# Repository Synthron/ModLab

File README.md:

# ModLab

## A modular station for your electronic workbench

The ModLab is designed to be housed in a 19" Rack with 3U.  
It is the improved version of the (failed) Arduino Workstation I built a long time ago.

But now It will be bigger, better and way too complicated.

---

[GitHub](https://github.com/Synthron/ModLab)
[Gitlab](https://gitlab.synthron.de/Synthron/ModLab)

---

**Work in Progress**

---

# To-Dos

## Repo

- [X] Rewrite documentation in english
  - [ ] Write better introduction
  - [ ] explain what exactly the ModLab is
  - [X] update changes for TFT
  - [X] Explain TFT Protocol
  - [ ] Attach Schematics
- [X] Cleanup Repo

---

## Hardware

- [X] Redesign modules with STM32
  - [x] Master Bus Controller with F767
    - [X] V1
      - [X] Review
      - [X] Ordered
      - [X] Assembled
    - [ ] V2
      - [ ] Change LCD connector
      - [ ] omit external SRAM
      - [ ] include header for Reset
  - [x] Diode/LED-Tester
    - [X] V1
    - [X] V2
  - [X] Variable Power Supply
    - [X] V1
    - [ ] V2
      - [X] Fix Relais Footprint
      - [X] Feedback Dividers for correct level
      - [ ] Review
      - [ ] Ordered
      - [ ] Assembled
  - [x] Symmetric Power Supply
    - [X] V1
    - [ ] V2
      - [X] fix negative channel
      - [X] fix CC LEDs
      - [ ] Review
      - [ ] Ordered
      - [ ] Assembled
  - [x] Waveform generator
  - [ ] DSO-138 clone?
  - [X] Electronic Load
  - [ ] Logic Tester
  - [ ] Continuity tester
  - [ ] Speaker Module
  - [x] Termination boards and Bus Extenders

---

## Software

- General
  - [X] Define CAN Protocol
    - [X] Define Command Structure
    - [X] Define Data Structure
- Master Bus Controller
  - [ ] STM32 code
    - [X] USB for Debug
    - [X] LCD
      - [X] Get Nextion Display working
        - [X] UI
        - [X] µC Interface
    - [ ] Busses
      - [X] CAN
      - [ ] SPI - No Usecase so far
      - [ ] I2C
      - [ ] DAC - No Usecase so far
      - [ ] RS485 - No Usecase so far
  - [ ] ESP32 code
    - [ ] comm with STM
    - [X] OTA
    - [ ] basic web interface
- Diode Tester code
  - [X] CAN
  - [X] Testing Sequence
  - [X] ADC
- SymPSU
  - [X] PWM Signals
  - [X] ADC
  - [X] CAN-Interface
- Power SMPS
  - [X] PWM Signals
  - [X] ADC
  - [X] CAN-Interface
- Waveform Generator
  - [X] PWM Signals
  - [X] AD9833
  - [X] CAN-Interface
- Power Monitor
  - [ ] Voltage Measurement
  - [ ] Current Measurement
  - [ ] I2C communication

---

ModLab Lib Tracker:

1. SymPSU
2. Diode-Tester
3. SMPS
4. Load
5. F-Gen

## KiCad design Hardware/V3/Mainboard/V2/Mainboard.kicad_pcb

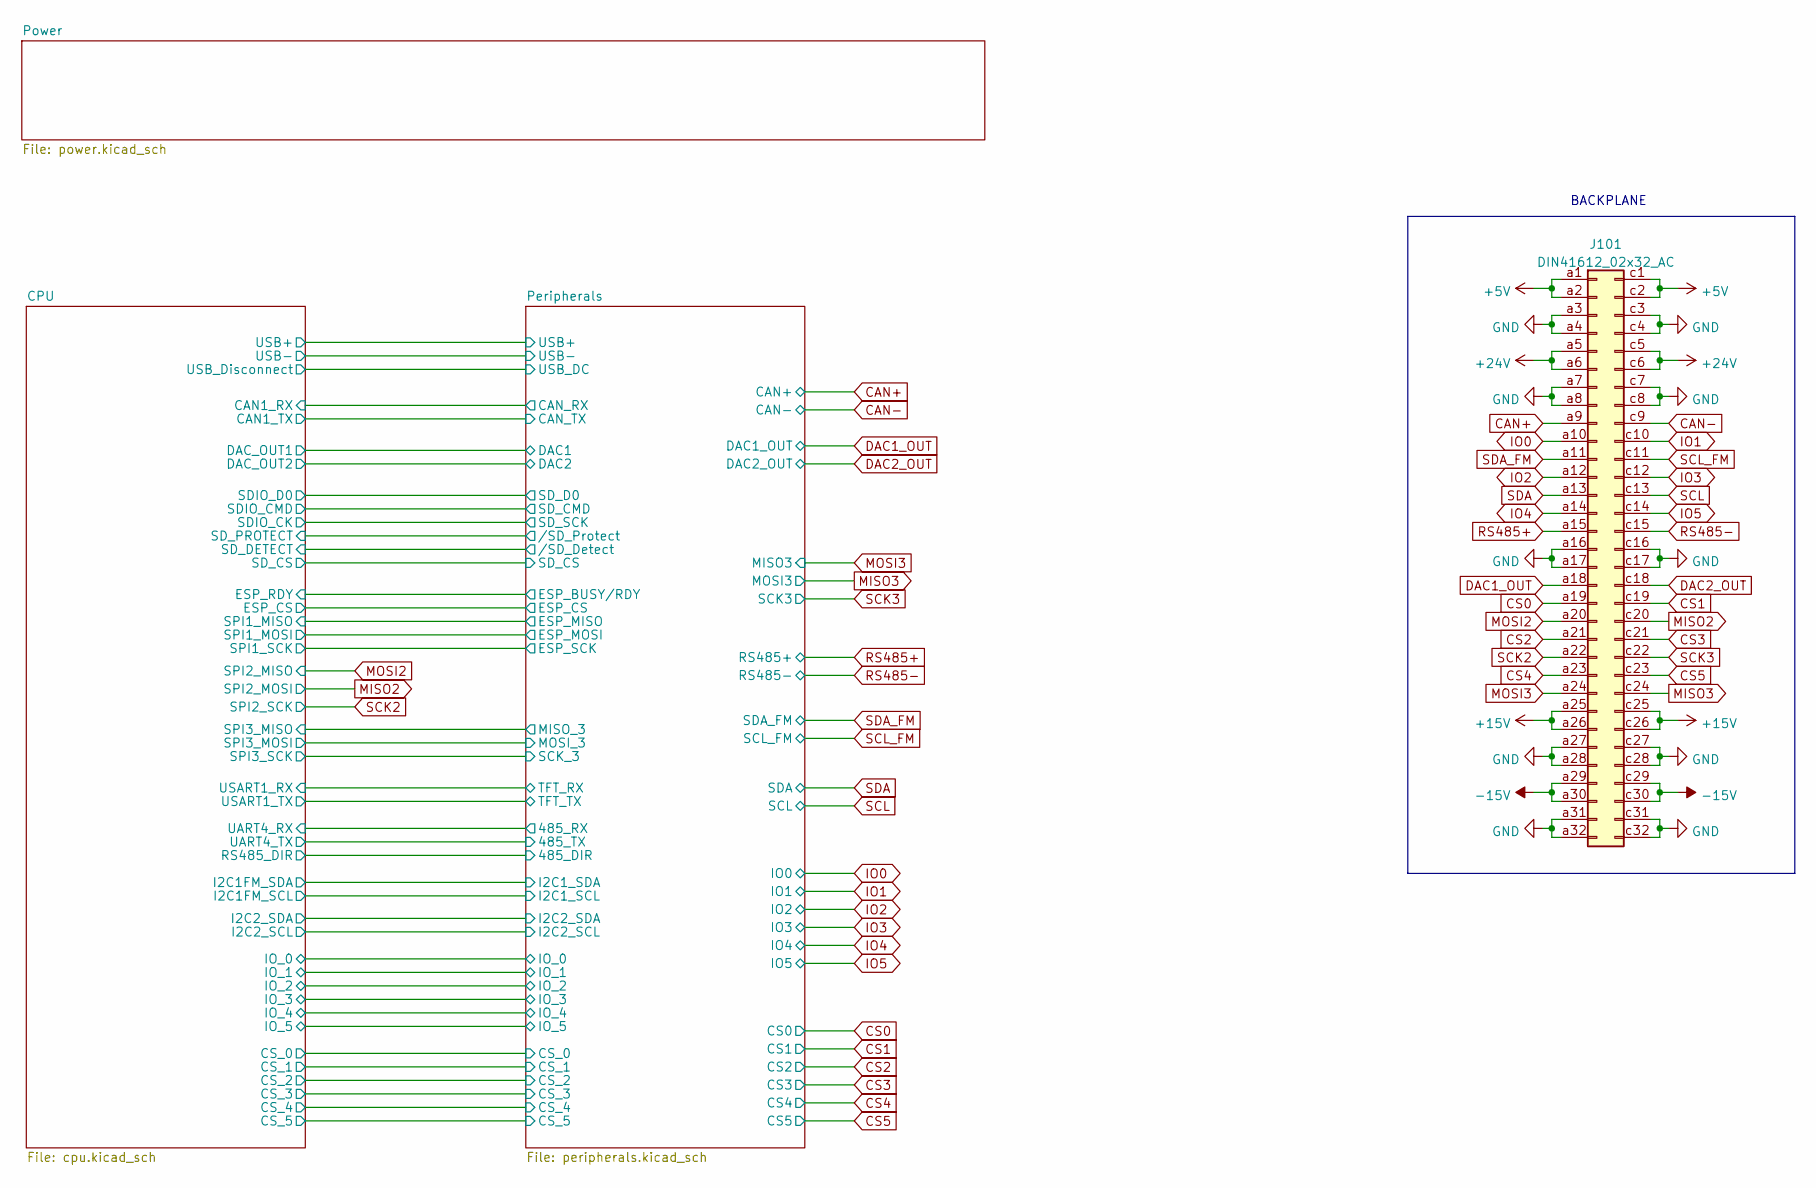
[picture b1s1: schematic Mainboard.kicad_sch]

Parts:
J101: DIN41612_02x32_AC; VG64_Euro

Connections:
+5V: J101.a1, J101.a2, J101.c1, J101.c2; also elsewhere on the board
+15V: J101.a25, J101.a26, J101.c25, J101.c26; also elsewhere on the board
+24V: J101.a5, J101.a6, J101.c5, J101.c6; also elsewhere on the board
-15V: J101.a29, J101.a30, J101.c29, J101.c30; also elsewhere on the board
CAN+: J101.a9; also elsewhere on the board
CAN-: J101.c9; also elsewhere on the board
CS0: J101.a19; also elsewhere on the board
CS1: J101.c19; also elsewhere on the board
CS2: J101.a21; also elsewhere on the board
CS3: J101.c21; also elsewhere on the board
CS4: J101.a23; also elsewhere on the board
CS5: J101.c23; also elsewhere on the board
DAC1_OUT: J101.a18; also elsewhere on the board
DAC2_OUT: J101.c18; also elsewhere on the board
GND: J101.a3, J101.a4, J101.a7, J101.a8, J101.a16, J101.a17, J101.a27, J101.a28, J101.a31, J101.a32, J101.c3, J101.c4, J101.c7, J101.c8, J101.c16, J101.c17, J101.c27, J101.c28, J101.c31, J101.c32; also elsewhere on the board
IO0: J101.a10; also elsewhere on the board
IO1: J101.c10; also elsewhere on the board
IO2: J101.a12; also elsewhere on the board
IO3: J101.c12; also elsewhere on the board
IO4: J101.a14; also elsewhere on the board
IO5: J101.c14; also elsewhere on the board
MISO2: J101.c20; also elsewhere on the board
MISO3: J101.c24; also elsewhere on the board
MOSI2: J101.a20; also elsewhere on the board
MOSI3: J101.a24; also elsewhere on the board
RS485+: J101.a15; also elsewhere on the board
RS485-: J101.c15; also elsewhere on the board
SCK2: J101.a22; also elsewhere on the board
SCK3: J101.c22; also elsewhere on the board
SCL: J101.c13; also elsewhere on the board
SCL_FM: J101.c11; also elsewhere on the board
SDA: J101.a13; also elsewhere on the board
SDA_FM: J101.a11; also elsewhere on the board

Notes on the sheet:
BACKPLANE

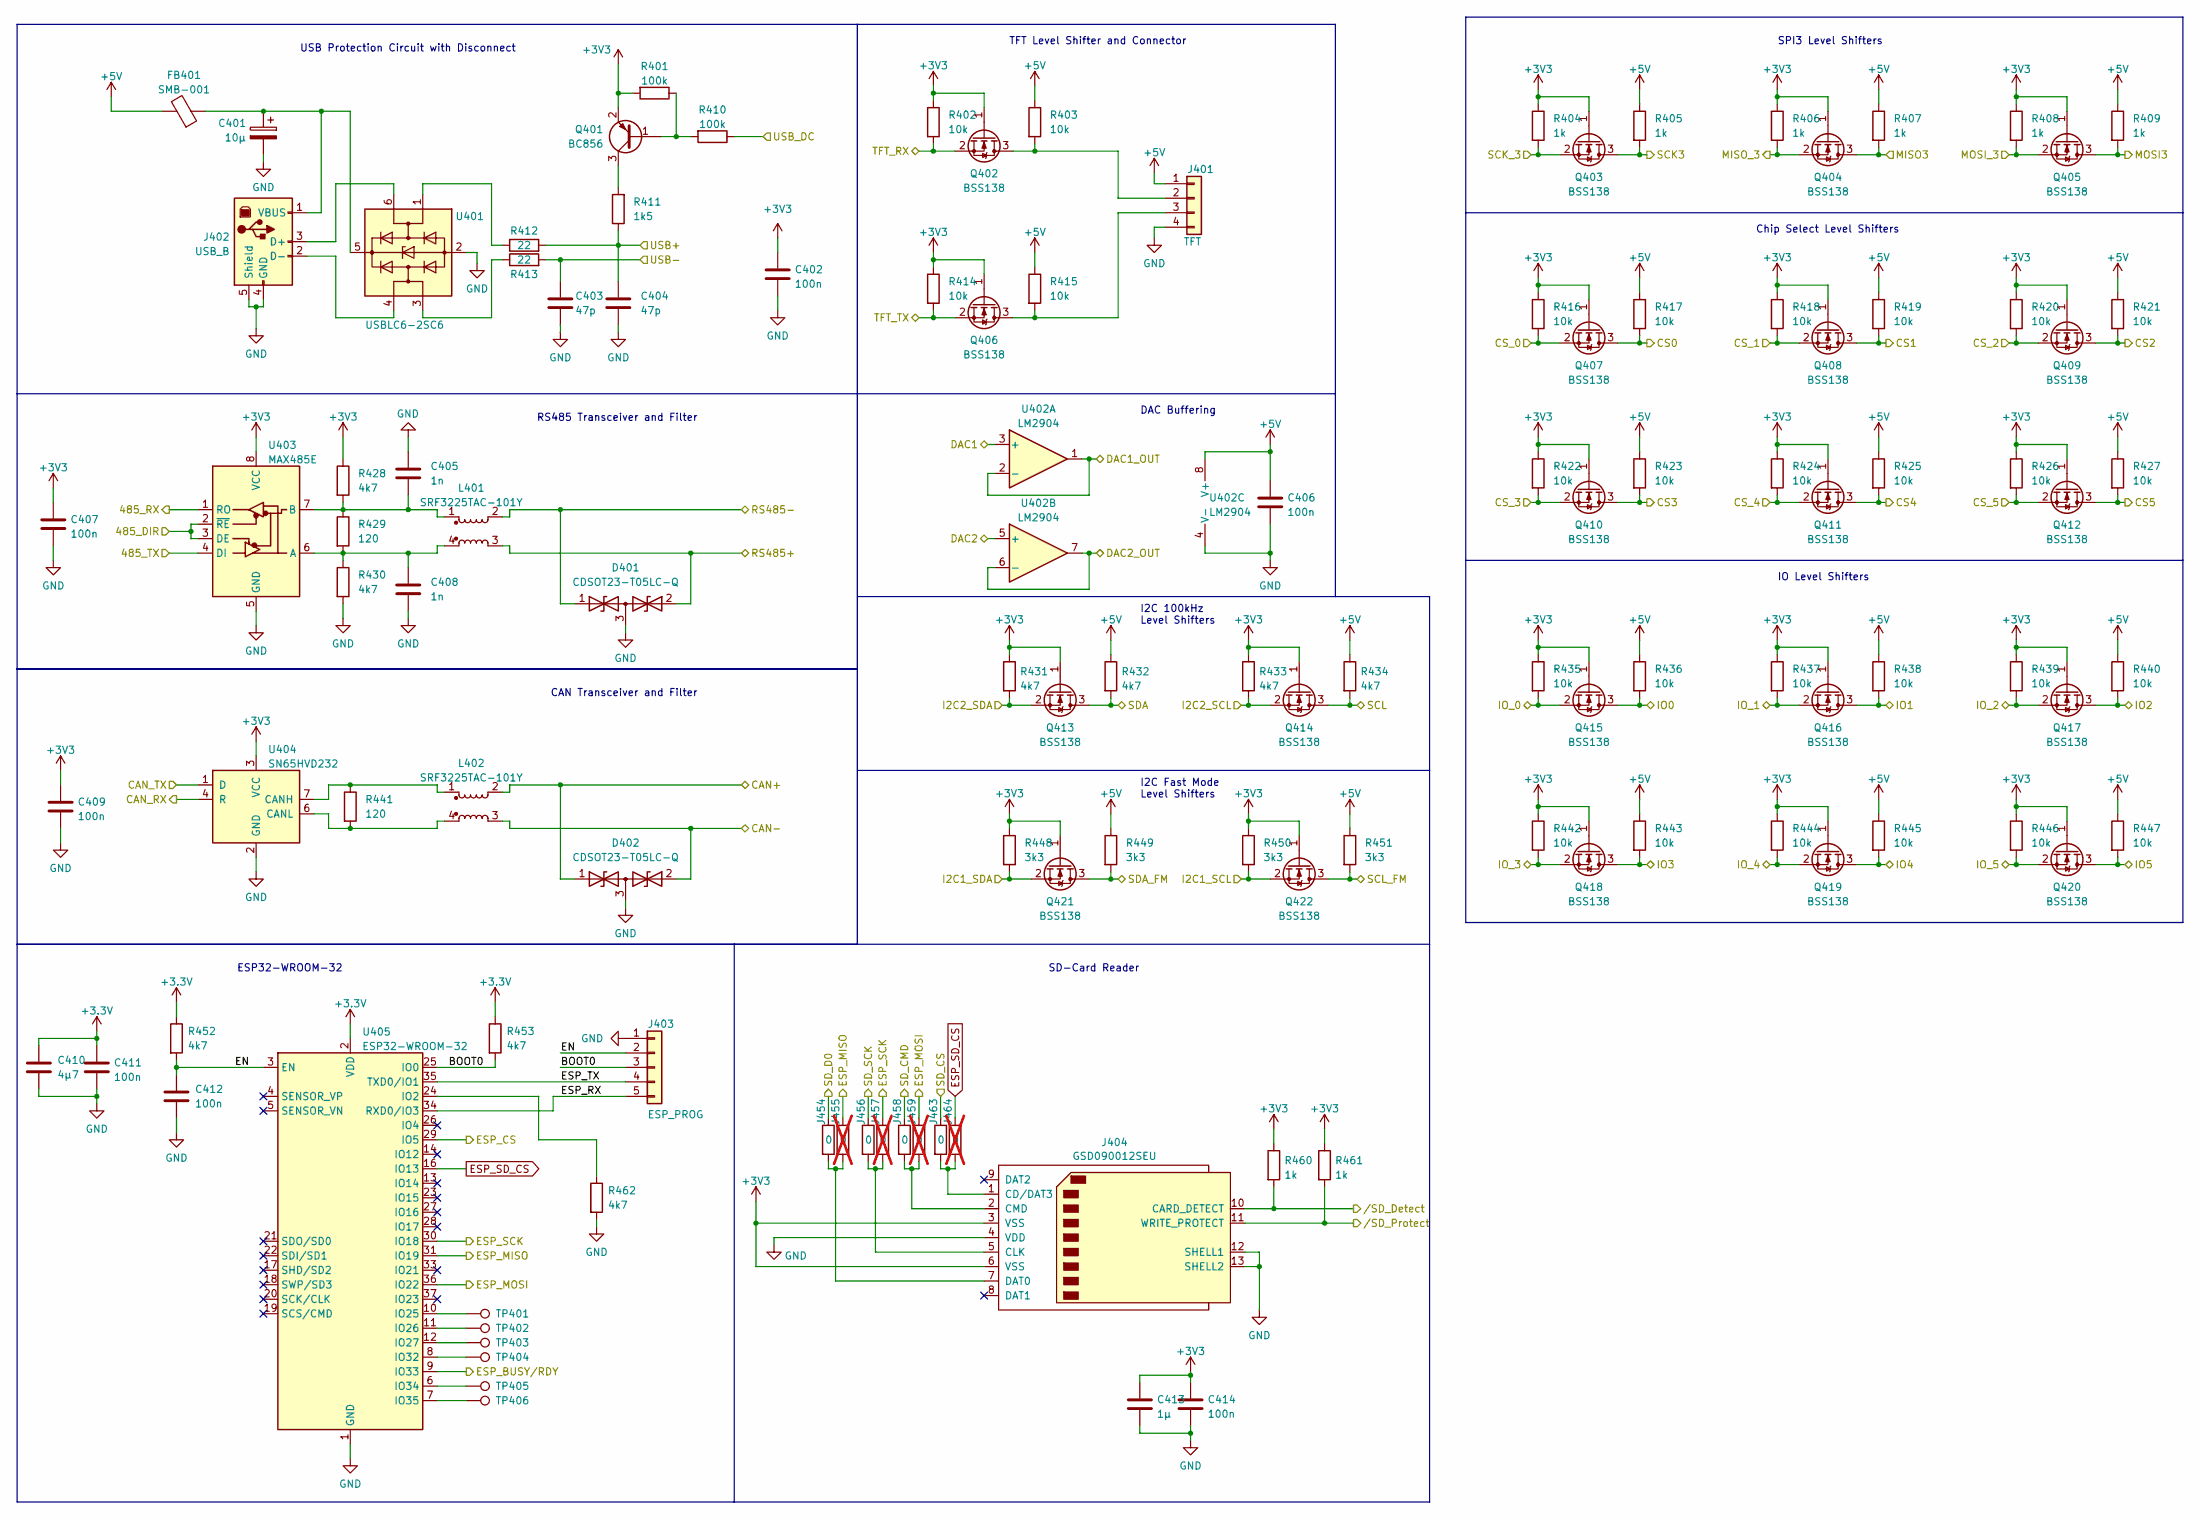
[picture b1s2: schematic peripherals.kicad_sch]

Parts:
C401: 10µ; CP_Elec_5x5.8
C402, C406, C407, C409, C411, C412, C414: 100n; C_0805_2012Metric
C403, C404: 47p; C_0805_2012Metric
C405, C408: 1n; C_0805_2012Metric
C410: 4µ7; C_0805_2012Metric
C413: 1µ; C_0805_2012Metric
D401, D402: CDSOT23-T05LC-Q; SOT-23
FB401: SMB-001
J401: TFT; JST_XH_B4B-XH-A_1x04_P2.50mm_Vertical
J402: USB_B; USB_B_OST_USB-B1HSxx_Horizontal
J403: ESP_PROG; JST_XH_B5B-XH-A_1x05_P2.50mm_Vertical
J404: GSD090012SEU
J454, J456, J458, J463: 0; SolderJumper-2_P1.3mm_Open_TrianglePad1.0x1.5mm
J455, J457, J459, J464: 0; SolderJumper-2_P1.3mm_Open_TrianglePad1.0x1.5mm; not fitted
L401, L402: SRF3225TAC-101Y; SRF3225TAC
Q401: BC856; SOT-23
Q402, Q403, Q404, Q405, Q406, Q407, Q408, Q409, Q410, Q411, Q412, Q413, Q414, Q415, Q416, Q417, Q418, Q419, Q420, Q421, Q422: BSS138; SOT-23
R401, R410: 100k; R_0805_2012Metric
R402, R403, R414, R415, R416, R417, R418, R419, R420, R421, R422, R423, R424, R425, R426, R427, R435, R436, R437, R438, R439, R440, R442, R443, R444, R445, R446, R447: 10k; R_0805_2012Metric
R404, R405, R406, R407, R408, R409, R460, R461: 1k; R_0805_2012Metric
R411: 1k5; R_0805_2012Metric
R412, R413: 22; R_0805_2012Metric
R428, R430, R431, R432, R433, R434, R452, R453, R462: 4k7; R_0805_2012Metric
R429, R441: 120; R_0805_2012Metric
R448, R449, R450, R451: 3k3; R_0805_2012Metric
TP401, TP402, TP403, TP404, TP405, TP406: TestPoint; TestPoint_Keystone_5000-5004_Miniature
U401: USBLC6-2SC6; SOT-23-6
U402: LM2904; SOIC-8_3.9x4.9mm_P1.27mm
U403: MAX485E; SOIC-8_3.9x4.9mm_P1.27mm
U404: SN65HVD232; SOIC-8_3.9x4.9mm_P1.27mm
U405: ESP32-WROOM-32

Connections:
+3.3V: C410.1, C411.1, R452.1, R453.1, U405.2 (VDD); also elsewhere on the board
+3V3: C402.1, C407.1, C409.1, C413.1, C414.1, J404.3 (VSS), J404.6 (VSS), Q401.2 (E), Q402.1 (G), Q403.1 (G), Q404.1 (G), Q405.1 (G), Q406.1 (G), Q407.1 (G), Q408.1 (G), Q409.1 (G), Q410.1 (G), Q411.1 (G), Q412.1 (G), Q413.1 (G), Q414.1 (G), Q415.1 (G), Q416.1 (G), Q417.1 (G), Q418.1 (G), Q419.1 (G), Q420.1 (G), Q421.1 (G), Q422.1 (G), R401.2, R402.1, R404.1, R406.1, R408.1, R414.1, R416.1, R418.1, R420.1, R422.1, R424.1, R426.1, R428.1, R431.1, R433.1, R435.1, R437.1, R439.1, R442.1, R444.1, R446.1, R448.1, R450.1, R460.1, R461.1, U403.8 (VCC), U404.3 (VCC); also elsewhere on the board
+5V: C406.1, FB401.2, J401.1, R403.1, R405.1, R407.1, R409.1, R415.1, R417.1, R419.1, R421.1, R423.1, R425.1, R427.1, R432.1, R434.1, R436.1, R438.1, R440.1, R443.1, R445.1, R447.1, R449.1, R451.1, U402.8 (V+); also elsewhere on the board
/CPU/CAN1_RX: U404.4 (R); also elsewhere on the board
/CPU/CAN1_TX: U404.1 (D); also elsewhere on the board
/CPU/CS_0: Q407.2 (S), R416.2; also elsewhere on the board
/CPU/CS_1: Q408.2 (S), R418.2; also elsewhere on the board
/CPU/CS_2: Q409.2 (S), R420.2; also elsewhere on the board
/CPU/CS_3: Q410.2 (S), R422.2; also elsewhere on the board
/CPU/CS_4: Q411.2 (S), R424.2; also elsewhere on the board
/CPU/CS_5: Q412.2 (S), R426.2; also elsewhere on the board
/CPU/DAC_OUT1: U402.3 (+); also elsewhere on the board
/CPU/DAC_OUT2: U402.5 (+); also elsewhere on the board
/CPU/ESP_CS: U405.29 (IO5); also elsewhere on the board
/CPU/ESP_RDY: U405.9 (IO33); also elsewhere on the board
/CPU/I2C1FM_SCL: Q422.2 (S), R450.2; also elsewhere on the board
/CPU/I2C1FM_SDA: Q421.2 (S), R448.2; also elsewhere on the board
/CPU/I2C2_SCL: Q414.2 (S), R433.2; also elsewhere on the board
/CPU/I2C2_SDA: Q413.2 (S), R431.2; also elsewhere on the board
/CPU/IO_0: Q415.2 (S), R435.2; also elsewhere on the board
/CPU/IO_1: Q416.2 (S), R437.2; also elsewhere on the board
/CPU/IO_2: Q417.2 (S), R439.2; also elsewhere on the board
/CPU/IO_3: Q418.2 (S), R442.2; also elsewhere on the board
/CPU/IO_4: Q419.2 (S), R444.2; also elsewhere on the board
/CPU/IO_5: Q420.2 (S), R446.2; also elsewhere on the board
/CPU/RS485_DIR: U403.2 (~RE), U403.3 (DE); also elsewhere on the board
/CPU/SDIO_CK: J456.1; also elsewhere on the board
/CPU/SDIO_CMD: J458.1; also elsewhere on the board
/CPU/SDIO_D0: J454.1; also elsewhere on the board
/CPU/SD_CS: J463.1; also elsewhere on the board
/CPU/SD_DETECT: J404.10 (CARD_DETECT), R460.2; also elsewhere on the board
/CPU/SD_PROTECT: J404.11 (WRITE_PROTECT), R461.2; also elsewhere on the board
/CPU/SPI1_MISO: J455.1, U405.31 (IO19); also elsewhere on the board
/CPU/SPI1_MOSI: J459.1, U405.36 (IO22); also elsewhere on the board
/CPU/SPI1_SCK: J457.1, U405.30 (IO18); also elsewhere on the board
/CPU/SPI3_MISO: Q404.2 (S), R406.2; also elsewhere on the board
/CPU/SPI3_MOSI: Q405.2 (S), R408.2; also elsewhere on the board
/CPU/SPI3_SCK: Q403.2 (S), R404.2; also elsewhere on the board
/CPU/UART4_RX: U403.1 (RO); also elsewhere on the board
/CPU/UART4_TX: U403.4 (DI); also elsewhere on the board
/CPU/USART1_RX: Q402.2 (S), R402.2; also elsewhere on the board
/CPU/USART1_TX: Q406.2 (S), R414.2; also elsewhere on the board
/CPU/USB+: C404.1, R411.1, R412.2; also elsewhere on the board
/CPU/USB-: C403.1, R413.2; also elsewhere on the board
/CPU/USB_Disconnect: R410.1; also elsewhere on the board
/Peripherals/BOOT0: J403.3, R453.2, U405.25 (IO0)
/Peripherals/EN: C412.1, J403.2, R452.2, U405.3 (EN)
/Peripherals/ESP_RX: J403.5, U405.34 (RXD0/IO3)
/Peripherals/ESP_TX: J403.4, U405.35 (TXD0/IO1)
CAN+: D402.1 (A1), L402.2; also elsewhere on the board
CAN-: D402.2 (A2), L402.3; also elsewhere on the board
CS0: Q407.3 (D), R417.2; also elsewhere on the board
CS1: Q408.3 (D), R419.2; also elsewhere on the board
CS2: Q409.3 (D), R421.2; also elsewhere on the board
CS3: Q410.3 (D), R423.2; also elsewhere on the board
CS4: Q411.3 (D), R425.2; also elsewhere on the board
CS5: Q412.3 (D), R427.2; also elsewhere on the board
DAC1_OUT: U402.1, U402.2 (-); also elsewhere on the board
DAC2_OUT: U402.6 (-), U402.7; also elsewhere on the board
ESP_SD_CS: J464.1, U405.16 (IO13)
GND: C401.2, C402.2, C403.2, C404.2, C405.1, C406.2, C407.2, C408.2, C409.2, C410.2, C411.2, C412.2, C413.2, C414.2, D401.3 (common), D402.3 (common), J401.4, J402.4 (GND), J402.5 (Shield), J403.1, J404.4 (VDD), J404.12 (SHELL1), J404.13 (SHELL2), R430.2, R462.2, U401.2 (GND), U402.4 (V-), U403.5 (GND), U404.2 (GND), U405.1 (GND), U405.15 (GND), U405.38 (GND), U405.39 (GND); also elsewhere on the board
IO0: Q415.3 (D), R436.2; also elsewhere on the board
IO1: Q416.3 (D), R438.2; also elsewhere on the board
IO2: Q417.3 (D), R440.2; also elsewhere on the board
IO3: Q418.3 (D), R443.2; also elsewhere on the board
IO4: Q419.3 (D), R445.2; also elsewhere on the board
IO5: Q420.3 (D), R447.2; also elsewhere on the board
MISO3: Q405.3 (D), R409.2; also elsewhere on the board
MOSI3: Q404.3 (D), R407.2; also elsewhere on the board
unnamed: J401.2, Q402.3 (D), R403.2
unnamed: J401.3, Q406.3 (D), R415.2
unnamed: J402.3 (D+), U401.6 (I/O1)
unnamed: J402.2 (D-), U401.4 (I/O2)
unnamed: C401.1, FB401.1, J402.1 (VBUS), U401.5 (VBUS)
unnamed: J404.1 (CD/DAT3), J463.2, J464.2
unnamed: J404.5 (CLK), J456.2, J457.2
unnamed: J404.2 (CMD), J458.2, J459.2
unnamed: J404.7 (DAT0), J454.2, J455.2
unnamed: Q401.1 (B), R401.1, R410.2
unnamed: Q401.3 (C), R411.2
unnamed: R412.1, U401.1 (I/O1)
unnamed: R413.1, U401.3 (I/O2)
unnamed: C408.1, L401.4, R429.2, R430.1, U403.6 (A)
unnamed: C405.2, L401.1, R428.2, R429.1, U403.7 (B)
unnamed: L402.1, R441.1, U404.7 (CANH)
unnamed: L402.4, R441.2, U404.6 (CANL)
unnamed: R462.1, U405.24 (IO2)
unnamed: TP401.1, U405.10 (IO25)
unnamed: TP402.1, U405.11 (IO26)
unnamed: TP403.1, U405.12 (IO27)
unnamed: TP404.1, U405.8 (IO32)
unnamed: TP405.1, U405.6 (IO34)
unnamed: TP406.1, U405.7 (IO35)
RS485+: D401.2 (A2), L401.3; also elsewhere on the board
RS485-: D401.1 (A1), L401.2; also elsewhere on the board
SCK3: Q403.3 (D), R405.2; also elsewhere on the board
SCL: Q414.3 (D), R434.2; also elsewhere on the board
SCL_FM: Q422.3 (D), R451.2; also elsewhere on the board
SDA: Q413.3 (D), R432.2; also elsewhere on the board
SDA_FM: Q421.3 (D), R449.2; also elsewhere on the board

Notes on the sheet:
DAC Buffering
ESP32-WROOM-32
SPI3 Level Shifters
USB Protection Circuit with Disconnect
I2C Fast Mode Level Shifters
I2C 100kHz Level Shifters
RS485 Transceiver and Filter
SD-Card Reader
CAN Transceiver and Filter
IO Level Shifters
Chip Select Level Shifters
TFT Level Shifter and Connector

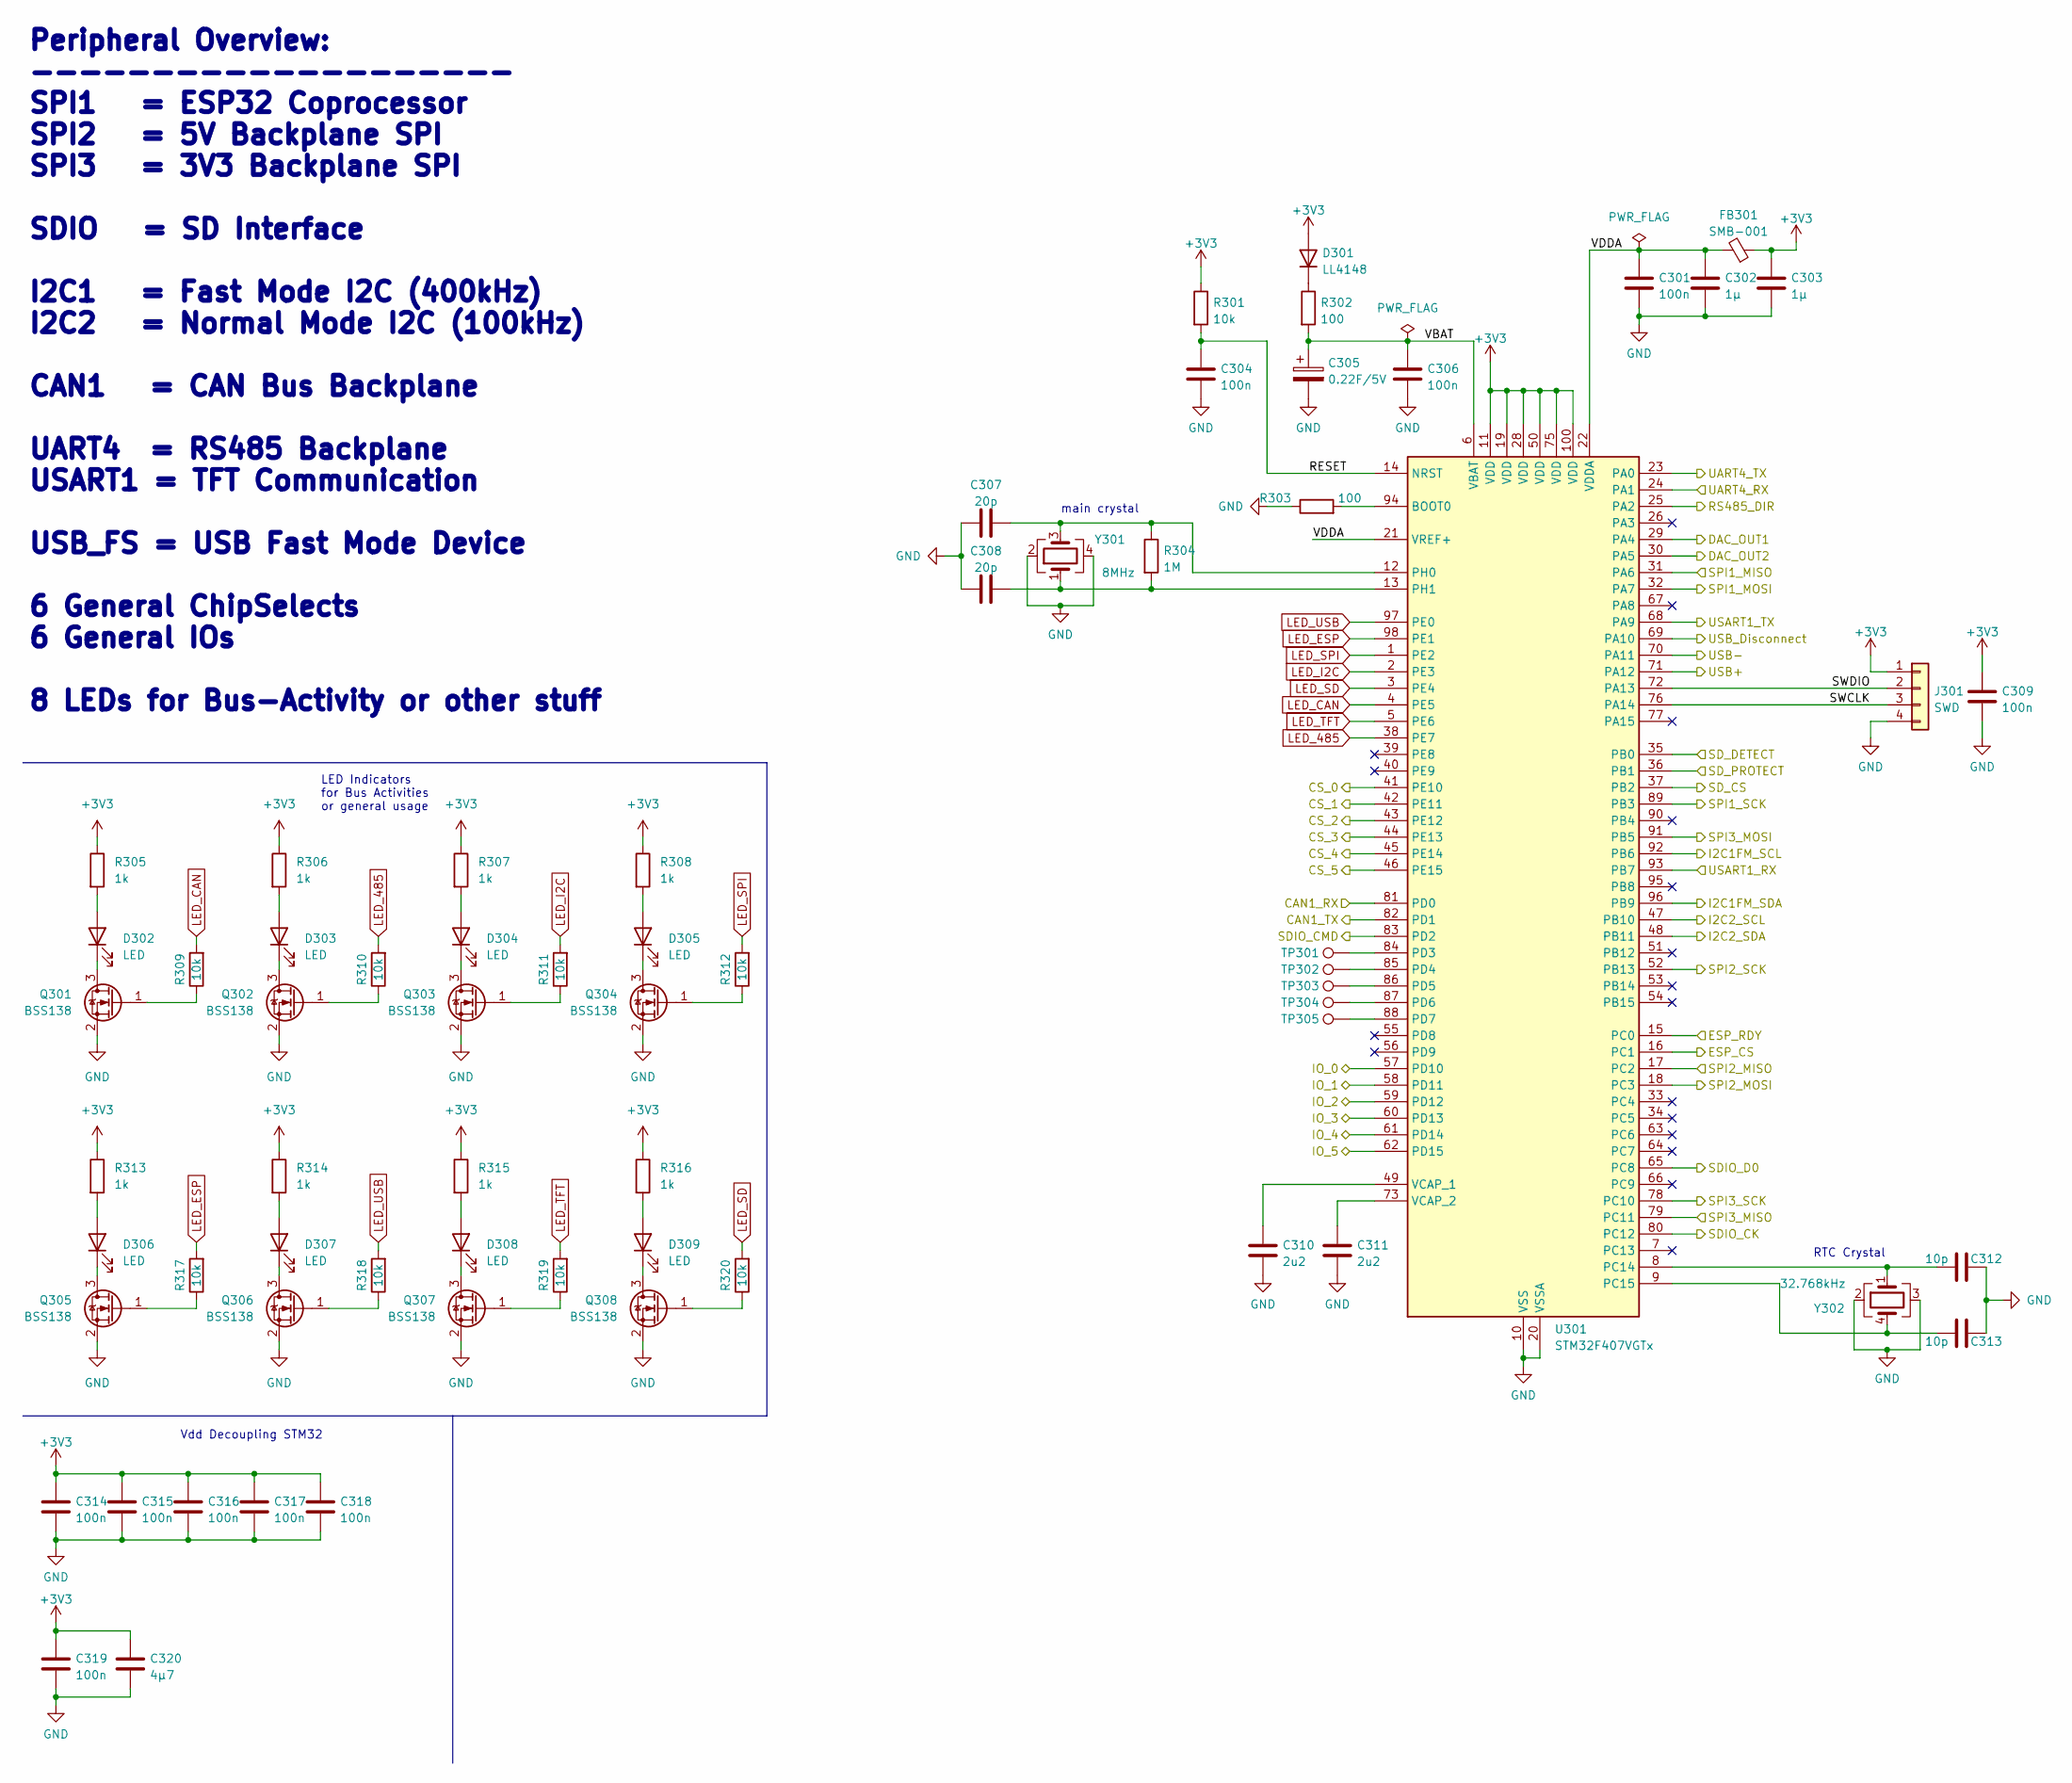
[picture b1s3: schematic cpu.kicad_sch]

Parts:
C301, C304, C306, C309, C314, C315, C316, C317, C318, C319: 100n; C_0805_2012Metric
C302, C303: 1µ; C_0805_2012Metric
C305: 0.22F/5V; CP_Elec_10x10.5
C307, C308: 20p; C_0805_2012Metric
C310, C311: 2u2; C_0805_2012Metric
C312, C313: 10p; C_0805_2012Metric
C320: 4µ7; C_0805_2012Metric
D301: LL4148; D_MiniMELF
D302, D303, D304, D305, D306, D307, D308, D309: LED; LED_D3.0mm
FB301: SMB-001
J301: SWD; JST_XH_B4B-XH-A_1x04_P2.50mm_Vertical
Q301, Q302, Q303, Q304, Q305, Q306, Q307, Q308: BSS138; SOT-23
R301, R309, R310, R311, R312, R317, R318, R319, R320: 10k; R_0805_2012Metric
R302, R303: 100; R_0805_2012Metric
R304: 1M; R_0805_2012Metric
R305, R306, R307, R308, R313, R314, R315, R316: 1k; R_0805_2012Metric
TP301, TP302, TP303, TP304, TP305: TestPoint; TestPoint_Keystone_5000-5004_Miniature
U301: STM32F407VGTx; LQFP-100_14x14mm_P0.5mm
Y301: 8MHz; Crystal_SMD_5032-4Pin_5.0x3.2mm
Y302: 32.768kHz; Crystal_SMD_SeikoEpson_MC306-4Pin_8.0x3.2mm

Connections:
+3V3: C303.1, C309.1, C314.1, C315.1, C316.1, C317.1, C318.1, C319.1, C320.1, D301.2 (A), FB301.1, J301.1, R301.1, R305.1, R306.1, R307.1, R308.1, R313.1, R314.1, R315.1, R316.1, U301.11 (VDD), U301.19 (VDD), U301.28 (VDD), U301.50 (VDD), U301.75 (VDD), U301.100 (VDD); also elsewhere on the board
/CPU/CAN1_RX: U301.81 (PD0); also elsewhere on the board
/CPU/CAN1_TX: U301.82 (PD1); also elsewhere on the board
/CPU/CS_0: U301.41 (PE10); also elsewhere on the board
/CPU/CS_1: U301.42 (PE11); also elsewhere on the board
/CPU/CS_2: U301.43 (PE12); also elsewhere on the board
/CPU/CS_3: U301.44 (PE13); also elsewhere on the board
/CPU/CS_4: U301.45 (PE14); also elsewhere on the board
/CPU/CS_5: U301.46 (PE15); also elsewhere on the board
/CPU/DAC_OUT1: U301.29 (PA4); also elsewhere on the board
/CPU/DAC_OUT2: U301.30 (PA5); also elsewhere on the board
/CPU/ESP_CS: U301.16 (PC1); also elsewhere on the board
/CPU/ESP_RDY: U301.15 (PC0); also elsewhere on the board
/CPU/I2C1FM_SCL: U301.92 (PB6); also elsewhere on the board
/CPU/I2C1FM_SDA: U301.96 (PB9); also elsewhere on the board
/CPU/I2C2_SCL: U301.47 (PB10); also elsewhere on the board
/CPU/I2C2_SDA: U301.48 (PB11); also elsewhere on the board
/CPU/IO_0: U301.57 (PD10); also elsewhere on the board
/CPU/IO_1: U301.58 (PD11); also elsewhere on the board
/CPU/IO_2: U301.59 (PD12); also elsewhere on the board
/CPU/IO_3: U301.60 (PD13); also elsewhere on the board
/CPU/IO_4: U301.61 (PD14); also elsewhere on the board
/CPU/IO_5: U301.62 (PD15); also elsewhere on the board
/CPU/RESET: C304.1, R301.2, U301.14 (NRST)
/CPU/RS485_DIR: U301.25 (PA2); also elsewhere on the board
/CPU/SDIO_CK: U301.80 (PC12); also elsewhere on the board
/CPU/SDIO_CMD: U301.83 (PD2); also elsewhere on the board
/CPU/SDIO_D0: U301.65 (PC8); also elsewhere on the board
/CPU/SD_CS: U301.37 (PB2); also elsewhere on the board
/CPU/SD_DETECT: U301.35 (PB0); also elsewhere on the board
/CPU/SD_PROTECT: U301.36 (PB1); also elsewhere on the board
/CPU/SPI1_MISO: U301.31 (PA6); also elsewhere on the board
/CPU/SPI1_MOSI: U301.32 (PA7); also elsewhere on the board
/CPU/SPI1_SCK: U301.89 (PB3); also elsewhere on the board
/CPU/SPI3_MISO: U301.79 (PC11); also elsewhere on the board
/CPU/SPI3_MOSI: U301.91 (PB5); also elsewhere on the board
/CPU/SPI3_SCK: U301.78 (PC10); also elsewhere on the board
/CPU/SWCLK: J301.3, U301.76 (PA14)
/CPU/SWDIO: J301.2, U301.72 (PA13)
/CPU/UART4_RX: U301.24 (PA1); also elsewhere on the board
/CPU/UART4_TX: U301.23 (PA0); also elsewhere on the board
/CPU/USART1_RX: U301.93 (PB7); also elsewhere on the board
/CPU/USART1_TX: U301.68 (PA9); also elsewhere on the board
/CPU/USB+: U301.71 (PA12); also elsewhere on the board
/CPU/USB-: U301.70 (PA11); also elsewhere on the board
/CPU/USB_Disconnect: U301.69 (PA10); also elsewhere on the board
/CPU/VBAT: C305.1, C306.1, R302.2, U301.6 (VBAT)
/CPU/VDDA: C301.1, C302.1, FB301.2, U301.21 (VREF+), U301.22 (VDDA)
GND: C301.2, C302.2, C303.2, C304.2, C305.2, C306.2, C307.1, C308.1, C309.2, C310.2, C311.2, C312.1, C313.1, C314.2, C315.2, C316.2, C317.2, C318.2, C319.2, C320.2, J301.4, Q301.2 (S), Q302.2 (S), Q303.2 (S), Q304.2 (S), Q305.2 (S), Q306.2 (S), Q307.2 (S), Q308.2 (S), R303.1, U301.10 (VSS), U301.20 (VSSA), U301.27 (VSS), U301.74 (VSS), U301.99 (VSS), Y301.2, Y301.4, Y302.2, Y302.3; also elsewhere on the board
LED_485: R310.2, U301.38 (PE7)
LED_CAN: R309.2, U301.4 (PE5)
LED_ESP: R317.2, U301.98 (PE1)
LED_I2C: R311.2, U301.2 (PE3)
LED_SD: R320.2, U301.3 (PE4)
LED_SPI: R312.2, U301.1 (PE2)
LED_TFT: R319.2, U301.5 (PE6)
LED_USB: R318.2, U301.97 (PE0)
MISO2: U301.18 (PC3); also elsewhere on the board
MOSI2: U301.17 (PC2); also elsewhere on the board
unnamed: D301.1 (K), R302.1
unnamed: D302.2 (A), R305.2
unnamed: D302.1 (K), Q301.3 (D)
unnamed: D303.2 (A), R306.2
unnamed: D303.1 (K), Q302.3 (D)
unnamed: D304.2 (A), R307.2
unnamed: D304.1 (K), Q303.3 (D)
unnamed: D305.2 (A), R308.2
unnamed: D305.1 (K), Q304.3 (D)
unnamed: D306.2 (A), R313.2
unnamed: D306.1 (K), Q305.3 (D)
unnamed: D307.2 (A), R314.2
unnamed: D307.1 (K), Q306.3 (D)
unnamed: D308.2 (A), R315.2
unnamed: D308.1 (K), Q307.3 (D)
unnamed: D309.2 (A), R316.2
unnamed: D309.1 (K), Q308.3 (D)
unnamed: Q301.1 (G), R309.1
unnamed: Q302.1 (G), R310.1
unnamed: Q303.1 (G), R311.1
unnamed: Q304.1 (G), R312.1
unnamed: Q305.1 (G), R317.1
unnamed: Q306.1 (G), R318.1
unnamed: Q307.1 (G), R319.1
unnamed: Q308.1 (G), R320.1
unnamed: R303.2, U301.94 (BOOT0)
unnamed: C312.2, U301.8 (PC14), Y302.1
unnamed: C313.2, U301.9 (PC15), Y302.4
unnamed: TP301.1, U301.84 (PD3)
unnamed: TP302.1, U301.85 (PD4)
unnamed: TP303.1, U301.86 (PD5)
unnamed: TP304.1, U301.87 (PD6)
unnamed: TP305.1, U301.88 (PD7)
unnamed: C307.2, R304.1, U301.12 (PH0), Y301.3
unnamed: C308.2, R304.2, U301.13 (PH1), Y301.1
unnamed: C310.1, U301.49 (VCAP_1)
unnamed: C311.1, U301.73 (VCAP_2)
SCK2: U301.52 (PB13); also elsewhere on the board

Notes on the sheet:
LED Indicators for Bus Activities or general usage
main crystal
Peripheral Overview: -------------------- SPI1 = ESP32 Coprocessor SPI2 = 5V Backplane SPI SPI3 = 3V3 Backplane SPI SDIO = SD Interface I2C1 = Fast Mode I2C (400kHz) I2C2 = Normal Mode I2C (100kHz) CAN1 = CAN Bus Backplane UART4 = RS485 Backplane USART1 = TFT Communication USB_FS = USB Fast Mode De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
RTC Crystal
Vdd Decoupling STM32

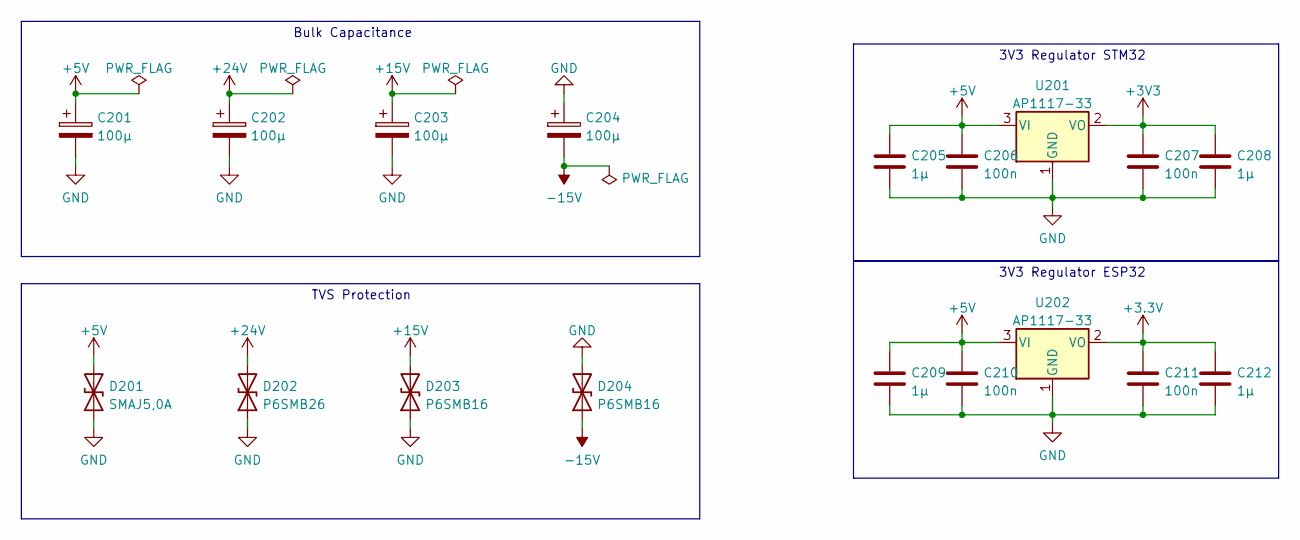
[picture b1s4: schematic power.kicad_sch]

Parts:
C201, C202, C203, C204: 100µ; CP_Radial_D8.0mm_P5.00mm
C205, C208, C209, C212: 1µ; C_0805_2012Metric
C206, C207, C210, C211: 100n; C_0805_2012Metric
D201: SMAJ5,0A; D_SMA
D202: P6SMB26; D_SMA
D203, D204: P6SMB16; D_SMA
U201, U202: AP1117-33; SOT-223-3_TabPin2

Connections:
+3.3V: C211.1, C212.1, U202.2 (VO); also elsewhere on the board
+3V3: C207.1, C208.1, U201.2 (VO); also elsewhere on the board
+5V: C201.1, C205.1, C206.1, C209.1, C210.1, D201.2 (A2), U201.3 (VI), U202.3 (VI); also elsewhere on the board
+15V: C203.1, D203.2 (A2); also elsewhere on the board
+24V: C202.1, D202.2 (A2); also elsewhere on the board
-15V: C204.2, D204.1 (A1); also elsewhere on the board
GND: C201.2, C202.2, C203.2, C204.1, C205.2, C206.2, C207.2, C208.2, C209.2, C210.2, C211.2, C212.2, D201.1 (A1), D202.1 (A1), D203.1 (A1), D204.2 (A2), U201.1 (GND), U202.1 (GND); also elsewhere on the board

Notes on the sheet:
3V3 Regulator STM32
3V3 Regulator ESP32
Bulk Capacitance
TVS Protection

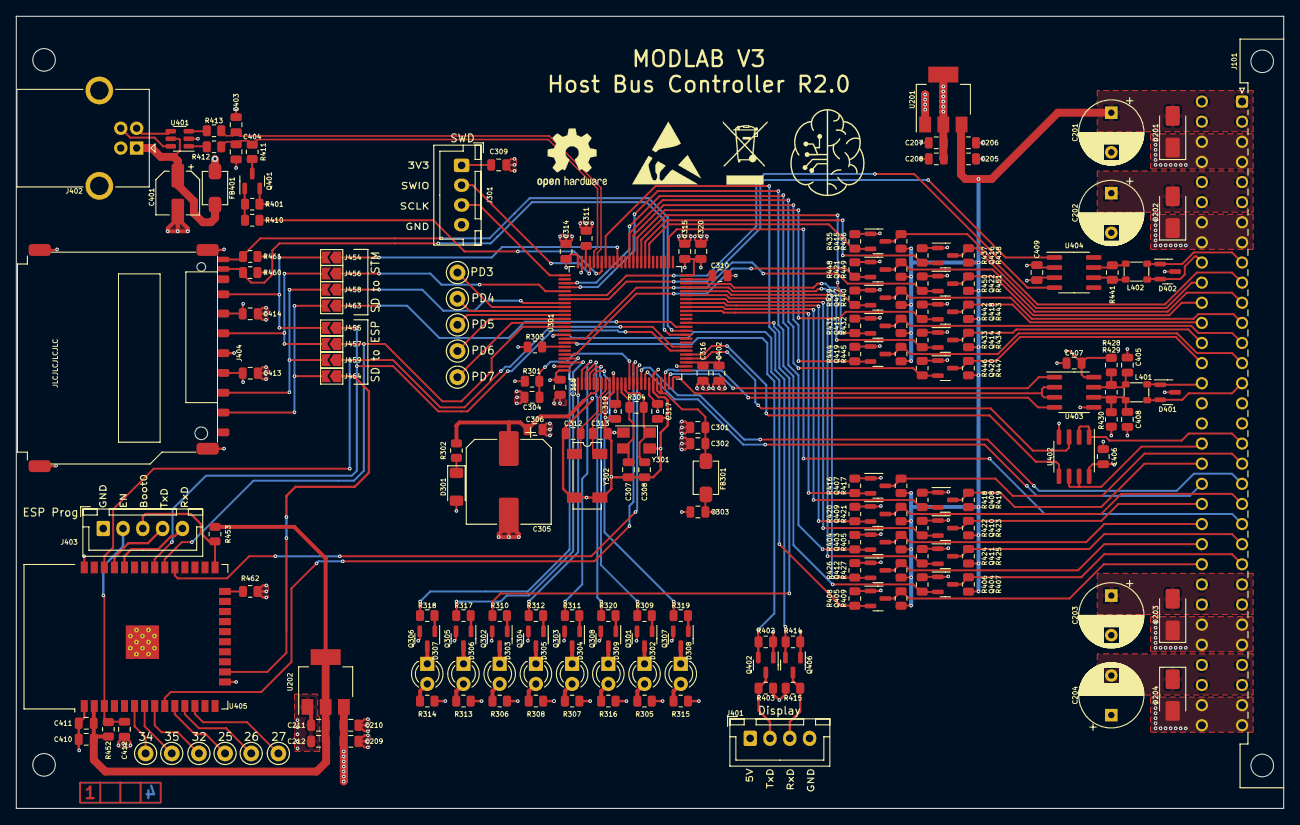
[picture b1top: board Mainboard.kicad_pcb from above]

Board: 4 copper layers, 160.0 x 100.0 mm, 207 parts (0 on the bottom side), 156 nets.

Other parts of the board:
Ref**: Val**; ladder_4

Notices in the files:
Software/Waveform/Src/main.c:
© Copyright (c) 2023 STMicroelectronics.
All rights reserved.
This software component is licensed by ST under BSD 3-Clause license,
the "License"; You may not use this file except in compliance with the
License. You may obtain a copy of the License at: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
(C) COPYRIGHT STMicroelectronics *****END OF FILE
